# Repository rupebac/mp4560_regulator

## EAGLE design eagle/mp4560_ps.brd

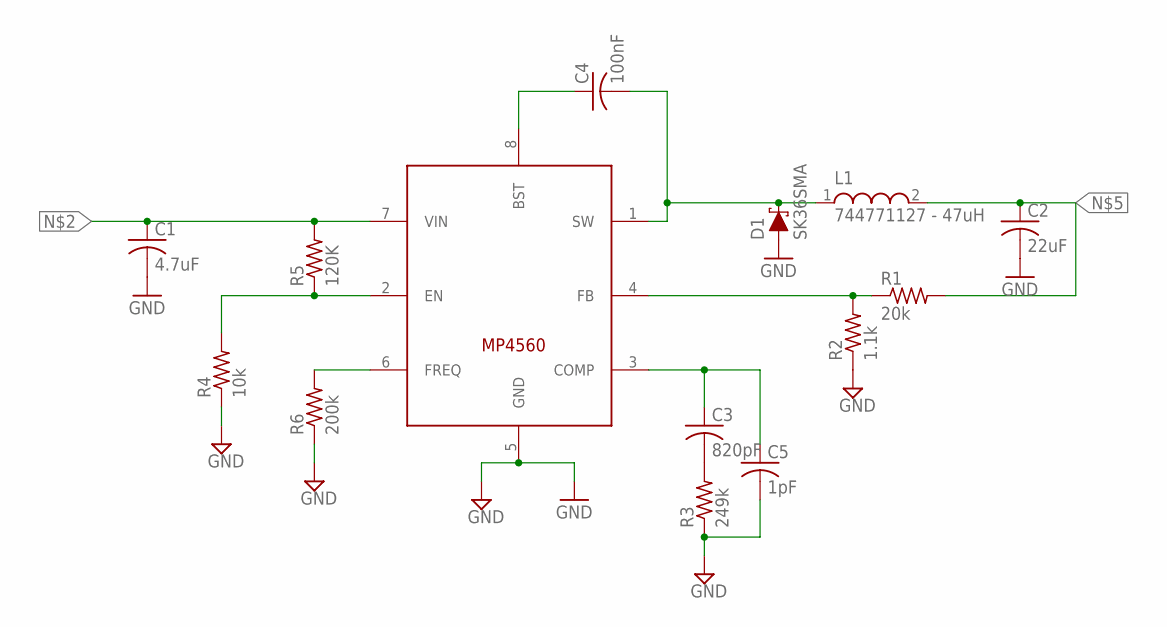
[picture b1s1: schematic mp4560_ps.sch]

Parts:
C1: 4.7uF; C1210
C2: 22uF; C1210
C3: 820pF; C0805
C4: 100nF; C0805
C5: 1pF; C0805
D1: SK36SMA; SMA-DIODE
L1: 744771127 - 47uH; WE-PD_1260/1245/1280/1210
R1: 20k; R0805
R2: 1.1k; R0805
R3: 249k; R0805
R4: 10k; R0805
R5: 120K; R0805
R6: 200k; R0805
U$1: MP4560; SOIC8

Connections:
GND: C1.2, C2.2, C5.2, D1.A, R2.1, R3.1, R4.1, R6.1, U$1.5 (GND)
unnamed: R4.2, R5.1, U$1.2 (EN)
unnamed: C1.1, R5.2, U$1.7 (VIN)
unnamed: R6.2, U$1.6 (FREQ)
unnamed: R1.1, R2.2, U$1.4 (FB)
unnamed: C2.1, L1.2, R1.2
unnamed: C4.1, U$1.8 (BST)
unnamed: C4.2, D1.C, L1.1, U$1.1 (SW)
unnamed: C3.2, R3.2
unnamed: C3.1, C5.1, U$1.3 (COMP)

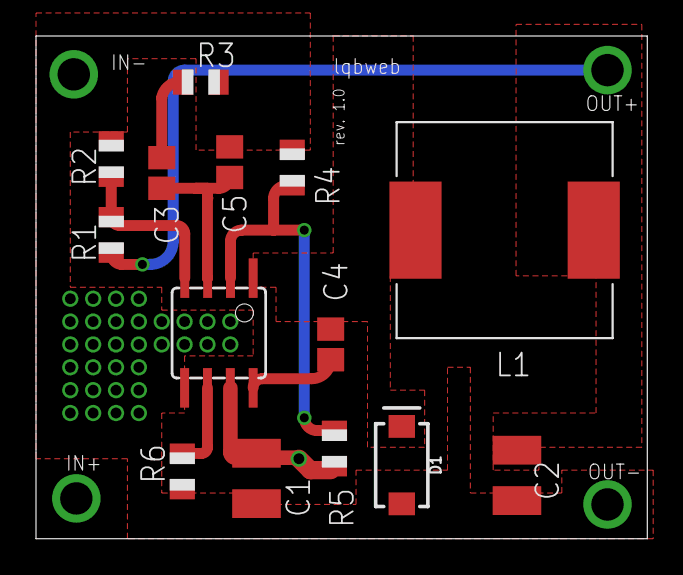
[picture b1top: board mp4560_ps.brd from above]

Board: 2 copper layers, 34.0 x 27.9 mm, 14 parts (0 on the bottom side), 10 nets.

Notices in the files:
parts and their libraries:
SparkFun-DiscreteSemi: Licensing: Creative Commons ShareAlike 4.0 International - https://creativecommons.org/licenses/by-sa/4.0
EAGLE-POWER_MAGNETICS-rev17a: Copyright: Würth Elektronik
